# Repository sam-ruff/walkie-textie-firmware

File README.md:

# Walkie-Textie Rust Firmware

ESP32-S3 firmware with WIO-SX1262 LoRa module using Embassy async runtime. Receives COBS-encoded binary commands over serial or BLE and supports LoRa TX/RX operations.

The wire protocol (command/response codec and COBS framing) lives in the shared [`wt-protocol`](https://github.com/sam-ruff/walkie-textie-protocol) crate, vendored here as a git submodule and used by both this firmware and the phone app so the two cannot drift. Clone with submodules:

```bash
git clone --recursive <repo-url>
# or, in an existing checkout:
git submodule update --init --recursive
```

## Building

### Prerequisites

Install the ESP Rust toolchain:

```bash
cargo install espup
espup install
source ~/export-esp.sh
```

You must run `source ~/export-esp.sh` in each new terminal session before building.

### Host Tests

Run unit tests on your development machine:

```bash
cargo t
# or: cargo test --target x86_64-unknown-linux-gnu
```

### Embedded Build (ESP32-S3)

Debug build:

```bash
cargo +esp build --features embedded -Zbuild-std=core,alloc
```

Release build:

```bash
cargo +esp build --features embedded --release -Zbuild-std=core,alloc
```

### Factory test build

Radio compliance measurements need the transmitter held on, or a steady run
of identical packets, which normal traffic never gives. Adding the
`factory-test` feature builds firmware that can do both. Never ship that
build.

```bash
cargo +esp build --features embedded,factory-test --release -Zbuild-std=core,alloc
```

Type one character into the debug serial port: `c` holds an unmodulated
carrier, `m` holds continuous LoRa modulation, `p` sends 64-byte test
packets with a second of silence after each, `s` stops. All three use the
configured frequency and power. The build also advertises over Bluetooth
every 20 ms. Its host tests run with
`cargo test --target x86_64-unknown-linux-gnu --features host-test,factory-test`.
It has not been run on a board yet.

### Flash

```bash
espflash flash --port /dev/ttyACM0 target/xtensa-esp32s3-none-elf/release/walkie-textie-rust-firmware
```

Or use cargo run (configured in `.cargo/config.toml`):

```bash
cargo +esp run --features embedded --release -Zbuild-std=core,alloc
```

To flash multiple devices at once:

```bash
./flash_devices.sh                           # Auto-detect and flash all
./flash_devices.sh /dev/ttyACM0 /dev/ttyACM2 # Flash specific ports
```

**If flashing fails**, put the device in bootloader mode:
1. Hold the **BOOT** button
2. Press and release **RESET**
3. Release **BOOT** button
4. Run the flash command again

**After flashing**, unplug and replug the USB cable. Verify the device is running by checking that two serial ports appear:

```bash
ls /dev | grep ACM
# Should show: ttyACM0 ttyACM1 (for one device)
# Or: ttyACM0 ttyACM1 ttyACM2 ttyACM3 (for two devices)
```

### Monitor

The firmware exposes two USB CDC-ACM serial ports:
- **CDC0** (e.g. `/dev/ttyACM0`): Data port for commands/responses
- **CDC1** (e.g. `/dev/ttyACM1`): Debug log output

To monitor the debug output after flashing:

```bash
# Open debug port (second ttyACM device)
picocom /dev/ttyACM1 -b 115200
```

Debug output includes startup messages and LoRa/BLE events:
```
Walkie-Textie v0.1.0 starting...
Device ID: A1B2C3
Starting tasks...
LoRa: Initialising radio...
LoRa: Radio initialised
BLE: Starting as 'WalkieTextie-A1B2C3'
BLE: Advertising...
All tasks started
LoRa TX: 'Hello World'
LoRa TX: Complete
LoRa RX: 'Reply' (RSSI: -45, SNR: 8)
BLE: Connected
BLE: Disconnected
```

To monitor both ports simultaneously, use two terminals or a tool like `tmux`:
```bash
# Terminal 1: Data port (for sending commands)
picocom /dev/ttyACM0 -b 115200
# Terminal 2: Debug port (for viewing logs)
picocom /dev/ttyACM1 -b 115200
# For a second device
picocom /dev/ttyACM3 -b 115200
```

## Bootloader

This firmware uses the ESP-IDF 2nd stage bootloader. The bootloader is pre-flashed on most ESP32-S3 development boards.

### espflash.toml and fresh clones

`espflash.toml` points espflash at the silent bootloader binary under
`bootloader/build/`, which is gitignored. On a fresh clone that file does
not exist and every `espflash flash` run from the repo directory fails with
a misleading "Error while connecting to device" - espflash reads the config
from the working directory and gives no missing-file error. Either build
the bootloader first (next section), comment the override out of
`espflash.toml`, or flash from outside the repo directory to fall back to
espflash's bundled bootloader.

### Flashing the Bootloader from Scratch

If you need to flash the bootloader (e.g., on a new chip or after corruption):

1. Install espflash:
   ```bash
   cargo install espflash
   ```

2. Download the ESP-IDF bootloader binary for ESP32-S3 from the espflash releases or build from ESP-IDF.

3. Flash the bootloader and partition table:
   ```bash
   espflash write-bin 0x0 bootloader.bin --port /dev/ttyACM0
   espflash write-bin 0x8000 partition-table.bin --port /dev/ttyACM0
   ```

Alternatively, espflash can flash a complete image including bootloader:
```bash
espflash flash --port /dev/ttyACM0 --bootloader bootloader.bin --partition-table partition-table.bin target/xtensa-esp32s3-none-elf/release/walkie-textie-rust-firmware
```

### Building a Silent Bootloader

By default, the ESP-IDF bootloader outputs log messages on boot. To disable this, build a custom bootloader with logging disabled using the project in `bootloader/`:

1. Install ESP-IDF (v5.2 or later):
   ```bash
   mkdir -p ~/esp
   cd ~/esp
   git clone -b v5.2.2 --recursive https://github.com/espressif/esp-idf.git
   cd esp-idf
   ./install.sh esp32s3
   ```

2. Build the silent bootloader:
   ```bash
   source ~/esp/esp-idf/export.sh
   cd bootloader
   idf.py set-target esp32s3
   idf.py build
   cp build/bootloader/bootloader.bin ../silent-bootloader-esp32s3.bin
   ```

3. Flash with the silent bootloader:
   ```bash
   espflash flash --port /dev/ttyACM0 \
       --bootloader silent-bootloader-esp32s3.bin \
       target/xtensa-esp32s3-none-elf/release/walkie-textie-rust-firmware
   ```

### Notes on ESP-IDF Bootloader Compatibility

The firmware includes an app descriptor (`esp_app_desc!` macro) required by the ESP-IDF bootloader for validation. The efuse block revision fields are set to accept all chip revisions (min=0, max=65535).

## Integration Tests

After flashing the firmware, run integration tests to verify functionality. Cargo aliases are provided for convenience and auto-detect data ports by default:

| Alias               | Description                |
|---------------------|----------------------------|
| `cargo integration` | Single-device serial tests |
| `cargo lora`        | Two-device LoRa tests      |
| `cargo ble-serial`  | BLE tests via serial       |
| `cargo ble-ble`     | BLE-to-BLE tests           |

Port auto-detection scans ttyACM devices and identifies the data port (CDC0) by sending a GetVersion command.

### Single-Device Tests

Tests basic command/response functionality:

```bash
# Auto-detect port (default)
cargo integration

# Or specify port manually
cargo integration --port /dev/ttyACM0
```

Options:
- `--port <PORT>`: Serial port (default: auto)
- `--baud <RATE>`: Baud rate (default: 115200)

The tests verify:
- GetVersion returns firmware version
- Invalid command returns error
- Multiple sequential commands work correctly

### Two-Device LoRa Tests

Tests bidirectional LoRa communication between two flashed devices:

```bash
# Auto-detect both ports (default)
cargo lora

# Or specify ports manually
cargo lora --port-a /dev/ttyACM0 --port-b /dev/ttyACM2
```

Options:
- `--port-a <PORT>`: Serial port for device A (default: auto)
- `--port-b <PORT>`: Serial port for device B (default: auto)
- `--baud <RATE>`: Baud rate (default: 115200)

The tests verify:
- A to B transmission
- B to A transmission
- Bidirectional ping-pong
- Multiple sequential messages
- Reliability (10 round trips)

## Hardware Configuration

| Pin    | Function         |
|--------|------------------|
| GPIO7  | SPI SCLK         |
| GPIO8  | SPI MISO         |
| GPIO9  | SPI MOSI         |
| GPIO41 | LoRa NSS (CS)    |
| GPIO39 | LoRa DIO1 (IRQ)  |
| GPIO42 | LoRa NRST        |
| GPIO40 | LoRa BUSY        |
| GPIO38 | LoRa RF_SW       |
| GPIO48 | LED (active low) |

TCXO voltage: 1.8V (configured via DIO3)

RF_SW is the receive enable of the Wio-SX1262's antenna switch. The driver
holds it high while the radio listens and low while it transmits or idles,
and DIO2 selects the transmit path.

## Command Protocol

Binary protocol with COBS encoding and zero byte delimiter:

```
[COBS-encoded payload][0x00]

Payload: [version: u8][cmd_id: u8][length: u16 LE][data][crc16: u16 LE]
```

Protocol version is currently `1`. The firmware will reject commands with mismatched versions.

### Commands

| ID   | Command            | Payload              | Response    | Description                        |
|------|--------------------|----------------------|-------------|------------------------------------|
| 0x01 | GetVersion         | None                 | Version     | Returns firmware version           |
| 0x03 | Reboot             | None                 | None        | Reboots the device (no response)   |
| 0x10 | LoraTx             | Data bytes (max 256) | TxComplete  | Transmits data over LoRa           |
| 0x11 | SetSpreadingFactor | sf (u8, 7-12)        | RadioConfig | Sets the LoRa spreading factor     |
| 0x12 | GetRadioConfig     | None                 | RadioConfig | Reads the active radio config      |

### Responses

| ID   | Response    | Payload                                                             | Description                              |
|------|-------------|---------------------------------------------------------------------|------------------------------------------|
| 0x01 | Version     | major, minor, patch (3 bytes)                                       | Firmware version response                |
| 0x10 | TxComplete  | None                                                                | LoRa transmission completed successfully |
| 0x11 | RxPacket    | data, rssi (i16 LE), snr (i8)                                       | Received LoRa packet (unsolicited)       |
| 0x12 | RadioConfig | freq_hz (u32 LE), sf (u8), bw_khz (u32 LE), cr (u8), tx_power (i8)  | Active radio configuration (11 bytes)    |
| 0x13 | TxRefused   | retry_after_secs (u32 LE)                                           | TX refused by the duty cycle limiter     |
| 0xFF | Error       | status code, original command ID                                    | Error response with status and cmd ID    |

### Response Format

Responses use the same frame structure as commands:

```
Payload: [version: u8][resp_id: u8][length: u16 LE][data][crc16: u16 LE]
```

### Unsolicited Responses

The firmware continuously listens for incoming LoRa packets in the background (100ms polling interval). When a packet is received, it is immediately pushed to the host as an unsolicited `RxPacket` response.

- Response ID: `0x11`
- Sequence ID: `0` (distinguishes unsolicited from request/response pairs)
- Payload: `[data bytes][rssi: i16 LE][snr: i8]`
- Max TX latency: 100ms (radio must exit RX mode to transmit)

The host must be ready to receive these at any time.

### Response Status Codes

| Code | Status           | Description                                        |
|------|------------------|----------------------------------------------------|
| 0x00 | Success          | Command executed successfully                      |
| 0x01 | InvalidCommand   | Unknown command ID                                 |
| 0x02 | InvalidLength    | Payload length invalid for command                 |
| 0x03 | CrcError         | CRC-16 checksum mismatch                           |
| 0x04 | InvalidVersion   | Protocol version mismatch                          |
| 0x05 | InvalidParameter | Parameter out of range (e.g. SF outside 7-12)      |
| 0x10 | LoraError        | LoRa radio error during operation                  |
| 0x11 | Timeout          | Operation timed out                                |

### Radio Configuration and Duty Cycle

The radio boots at 869.525 MHz, spreading factor 10, 125 kHz bandwidth, coding
rate 4/8 and +22 dBm. The spreading factor can be changed at runtime with
`SetSpreadingFactor` (7-12); it is not persisted and reverts to SF10 on reboot.
Both radios in a link must use the same spreading factor and bandwidth, so a
radio built before the bandwidth changed from 250 kHz cannot hear one built
after.

The bandwidth is half the 250 kHz sub-band on purpose. EN 300 220-2 wants the
occupied bandwidth inside the sub-band at every spreading factor and
temperature, and a 250 kHz signal leaves no room. SF10 at 125 kHz has the same
symbol time and sensitivity as SF11 at 250 kHz, and about nine tenths of its
bit rate.

Transmissions are checked against the EU duty cycle rules (ERC 70-03) for the
sub-band containing the configured frequency; 869.4-869.65 MHz allows 10%
airtime per sliding hour (360 s). Spent airtime is tracked with the Semtech
time-on-air formula, and a `LoraTx` that would exceed the remaining budget is
refused without transmitting: the firmware replies `TxRefused` with the number
of seconds until enough budget frees up (`0xFFFFFFFF` if the packet exceeds the
entire hourly budget). At SF10 a full 255-byte packet costs about 3.57 s of
airtime, so roughly 100 of them fit in an hour; lower spreading factors are far
cheaper.

### Example Frames

All examples show the complete COBS-encoded frame including the zero delimiter.

**GetVersion Command:**
```
Raw:    01 01 00 00 84 41       (version=1, cmd=0x01, len=0, crc=0x4184)
COBS:   03 01 01 01 03 84 41 00
```

**GetVersion Response (v0.1.0):**
```
Raw:    01 01 03 00 00 01 00 22 20    (version=1, resp=0x01, len=3, payload=[0,1,0], crc=0x2022)
COBS:   04 01 01 03 01 02 01 03 22 20 00
```

**Reboot Command:**
```
Raw:    01 03 00 00 e4 2f       (version=1, cmd=0x03, len=0, crc=0x2fe4)
COBS:   03 01 03 01 03 e4 2f 00
```

**LoraTx Command ("Hello"):**
```
Raw:    01 10 05 00 48 65 6c 6c 6f e6 64    (crc=0x64e6)
COBS:   04 01 10 05 08 48 65 6c 6c 6f e6 64 00
```

**Error Response (InvalidCommand for cmd 0xFE):**
```
Raw:    01 ff 02 00 01 fe 87 cf    (status=0x01, original_cmd=0xFE, crc=0xcf87)
COBS:   04 01 ff 02 05 01 fe 87 cf 00
```

### CRC-16 Calculation

The CRC-16 uses the XMODEM polynomial (0x1021) with initial value 0x0000. The CRC is calculated over the bytes: `[version][cmd_id][length_lo][length_hi][payload...]`.

Python example:
```python
import crcmod
crc16 = crcmod.predefined.mkCrcFun('xmodem')
checksum = crc16(bytes([0x01, 0x01, 0x00, 0x00]))  # GetVersion: 0x4184
```

### COBS Encoding

COBS (Consistent Overhead Byte Stuffing) encodes data to eliminate zero bytes, using 0x00 as frame delimiter. The firmware uses the `corncobs` implementation which appends the zero delimiter automatically.

Python example:
```python
from cobs import cobs
raw_frame = bytes([0x01, 0x01, 0x00, 0x00, 0x84, 0x41])
encoded = cobs.encode(raw_frame) + b'\x00'  # Add delimiter
```

## Bluetooth LE

The firmware advertises as "WalkieTextie" and provides a Nordic UART Service (NUS) for command/response communication alongside serial.

### Nordic UART Service UUIDs

| Characteristic | UUID                                 |
|----------------|--------------------------------------|
| Service        | 6E400001-B5A3-F393-E0A9-E50E24DCCA9E |
| RX (write)     | 6E400002-B5A3-F393-E0A9-E50E24DCCA9E |
| TX (notify)    | 6E400003-B5A3-F393-E0A9-E50E24DCCA9E |

### Usage

1. Scan for and connect to "WalkieTextie"
2. Enable notifications on the TX characteristic
3. Write COBS-encoded commands to the RX characteristic
4. Receive COBS-encoded responses via TX notifications

The same binary protocol is used over BLE as over serial. Commands sent via BLE receive responses via BLE; unsolicited LoRa RX packets are only sent to serial.

Compatible apps: nRF Connect, any app supporting NUS.

## Architecture

The firmware uses esp-rtos with Embassy async tasks and channel-based communication:

- **Serial Reader Task**: Reads USB serial, parses COBS frames, sends commands to channel
- **Serial Writer Task**: Receives responses from channel, encodes and writes to USB serial
- **LoRa Task**: Continuously listens for LoRa packets (100ms polling), pushes received packets immediately to serial. Processes TX commands when available with max 100ms latency.
- **LED Task**: Flashes LED on TX/RX events via channel (non-blocking)
- **BLE Host Task**: Manages BLE advertising, connections, and Nordic UART Service. Routes commands to the same channel as serial.

Traits (`LoraRadio`, `SerialPort`) allow unit testing with mock implementations.

## CI/CD

GitHub Actions runs on every push to `main`:

1. **Test**: Runs unit tests (`cargo test`)
2. **Build**: Builds release firmware using ESP toolchain
3. **Release**: Creates GitHub releases via semantic-release

Releases are triggered by conventional commit messages:
- `feat: ...` - minor version bump
- `fix: ...` - patch version bump
- `feat!: ...` or `BREAKING CHANGE:` - major version bump

The firmware binary is attached to each GitHub release.

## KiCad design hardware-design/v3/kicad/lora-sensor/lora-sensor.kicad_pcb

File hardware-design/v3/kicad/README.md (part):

# LoRa sensor board in KiCad (V3.1)

The designer's PCB_V3 arrived as fabrication files only: Gerbers, a BOM, a
placement file and pictures. There was nothing to edit. This folder rebuilds
that board as a KiCad 10 project from those files, then applies the changes
from our review of 11 September 2026. The result is called V3.1.

The design passes every check that can be made without a board in hand, but no
board has been made from it. The designer has not seen this version and
nothing here has been sent to him. Two jobs need the real thing: tuning the
868 MHz antenna match on a VNA, and the CE tests in `CE_TESTING.md`. One
finding was about the firmware and not the board: its 250 kHz LoRa bandwidth
did not fit the 250 kHz sub-band it transmits in. The firmware now uses
125 kHz, a change that has not yet been on a board. `CE_TESTING.md` has the
figures.

JLCPCB places every part. Nothing is left to solder when the boards arrive.
One part, the LoRa module, has to be sent to JLCPCB first, because they do not
stock it.

One thing is worth knowing before a board exists. The power mux
disconnects both supplies for some microseconds each time USB is plugged in
or pulled out with a battery fitted. On a nearly flat battery, with a radio
transmitting, that can stop the converter, and the supervisor then resets the
ESP32. Firmware should expect to be restarted by a change of supply. The
figures are under "On the first boards".

## What is here

`lora-sensor/` is the KiCad project: schematic, board, and its own symbol and
footprint libraries. Open `lora-sensor.kicad_pro` with KiCad 10.

`fab/` is what goes to the factory: Gerbers and drill files (also zipped), a
BOM and a placement file with JLCPCB's column names, and PDFs of the schematic
and the assembly drawing. There are four orders, which share the Gerbers and
differ in what is fitted:

| Order | Files | What it is for |
| --- | --- | --- |
| node | `fab/BOM.csv`, `fab/CPL.csv` | The default. R37 holds the converter on, for firmware that never signals the wake timer, such as the radio firmware in this repo |
| timed | `fab/timed/` | R37 left out, so the wake timer cuts the power between readings. For firmware that signals DONE |
| antenna-test | `fab/antenna-test/` | The U.FL connector and its link fitted and the radio's link left out, for measuring the antenna on a VNA. Never power one of these |
| bench-test | `fab/bench-test/` | The U.FL connector and its link fitted and the two antenna matching parts left out, for the conducted compliance tests |

`as-delivered/` is PCB_V3 exactly as the designer delivered it, imported into
KiCad so it can be opened, measured and compared. Plotted back out, its copper
matches his Gerbers to within 4 micrometres. Running DRC on it shows his
outline, drill and thermal-relief problems directly.

`tools/` builds all of the above. `datasheets/` holds the documents the layout
and the part changes rest on: the drawings of the USB plug and of the plug the
designer used, the Pulse antenna datasheet, the TPS631000, TPS2116, TPS2595
and TLV803 datasheets, and the datasheet of the MOSFET that replaced the
brief's. `CE_TESTING.md` is how to run the compliance tests on this board.

## The project is generated

Everything in `lora-sensor/` and `fab/` is written by `tools/build.py` from
`tools/design.py`, which lists every part, its position, its nets and every
track. The board is routed by hand: each track and via is written out there
with the reason for its path, and no autorouter runs. Change the design there
and rebuild. An edit made in KiCad is lost at the next build. Two builds of
the same design write the same files, so a diff in git is a real change.

If you would rather carry on in KiCad by hand, that works too: the project is
complete and passes its checks. Stop running the build after that.

```bash
cd hardware-design/v3/kicad
uv venv --python /usr/bin/python3 --system-site-packages .venv
uv pip install --python .venv/bin/python -r tools/requirements.txt
.venv/bin/python tools/build.py
```

The Python has to be the one KiCad's `pcbnew` module is installed for, which
is why the virtual environment is allowed to see system packages. The build
takes under a minute and stops at the first failing step. A warning fails it
the same as an error. A part that is new to the BOM needs `--fetch` once, to
download JLCPCB's library entry for it. These are the checks it ends on:

- KiCad's ERC on the schematic, and DRC on the board with the board compared
  against the schematic.
- The rules the routing was drawn to. Only the feed, its match and ground go
  near the 868 MHz feed. No top-layer track runs under the ESP32 module or
  between the timer's pins. A line may have 2.5 mm of top-layer track under
  the LoRa module to reach its pad and no more. The log lists each long line
  with its length on each layer and its vias.
- The firmware in this repo against the board. The pin numbers are read from
  `src/main.rs` and each is followed to the part it has to reach, GPIO38 to
  the LoRa module's RF_SW pin among them. The level each output starts at
  is checked too.
- Every part of every order has a JLCPCB part number and a row in the
  placement file. A part with neither would be left for someone to solder.
- Every placed part against JLCPCB's own footprint for its part number, at
  the position and rotation in the placement file. A part that would be
  fitted turned shows up as pads that miss. Each connected pad's function is
  compared with JLCPCB's symbol for the part as well, so a substitute with
  another pinout is caught.
- The values that set the 3.3 V rail, the wake-up interval, the voltage at
  which the USB input's switch passes power, its current limit and how fast
  it raises its output. Each is worked out at the worst case of the
  tolerances, against the datasheet formulas. The reset supervisor's
  threshold is checked against that rail.
- The power mux: that its pins put it in the mode that passes the higher
  supply, and how far its output falls while it changes from one supply to
  the other (`tools/supply_change.py`). These two checks and the USB input
  check below run for every order that is powered, with the parts it fits,
  and hold each to the same marks.
- For an order that leaves the rail to the wake timer, what the battery
  still feeds while the rail is off, added up from the makers' figures. If
  that is over the brief's 5 uA the log prints a RISK line. It does not
  stop the build, because the capacitors' share is a limit with no typical
  figure and only a measurement settles it.
- The Gerbers and drill file themselves: one closed rectangular outline, the
  two slots for the plug's legs, a board edge at either end of its tolerance
  still letting the widest leg into them, solder paste on the plug's pads
  and on the land round each leg with none of it on bare board, the inner
  planes 0.3 mm or more from those slots, 0.1 mm or more of solder mask
  between any two openings, no hole in a pad, the antenna area clear, the
  ground plane in one piece.
- The numbers behind the radio layout: feed impedance, antenna land pattern
  and the ESP32 antenna's overhang. Then what the datasheets predict for
  radiated power and harmonics at the power the firmware sets, against the
  legal limits. It also models the firmware's LoRa signal against the
  sub-band it uses and prints a RISK line when the fit is poor. That line
  does not stop the build either, because the remedy is a firmware setting.
- What the layout decides about emissions and static discharge: the area of
  the converter's switching loops and the field they could radiate, and the
  voltage a discharge to the plug's shell puts on the capacitor behind it.
  The same step models the ring on the USB input when the board is plugged
  into a live supply, and checks that only parts rated for it are ahead of
  the protection switch. It models a plug that loses contact and makes it
  again as well, when the switch is on and the ring reaches what is behind
  it, with the mux on USB and with the mux gone back to the battery. That
  ring has to stay 5 per cent under the 6 V those parts allow, and under
  6 V with less to damp it than the model assumes.
- The battery and sensor connectors: pin 1 where JST's drawing puts it, and
  a silkscreen legend that names the net on each pad.

## Before ordering

- Send the LoRa modules to JLCPCB before placing the order. U11 has to be
  the Wio-SX1262 without the antenna connector, Seeed part 113991436. JLCPCB
  does not stock it. Their library has an entry for parts of that number
  that customers send in, C9900285183, and the BOM carries it. If JLCPCB
  gives your modules another number when they book them in, change `lcsc`
  on U11 in `tools/design.py` and rebuild. The module with the connector
  (their C55348741, none in stock on 10 November 2026) leaves the antenna
  pad unconnected and will not do. No other LoRa module JLCPCB stocks has
  this module's pads or the same control pins.
- Choose JLCPCB's standard assembly service, not the economic one. The USB
  plug (J1, C530607) is listed for standard assembly only, with a fixture,
  because its shell hangs 10.7 mm over the board edge.
- Tell JLCPCB in the order's remarks that two parts hang over the board. J1
  overhangs the left edge by 10.7 mm between 24 and 36 mm from the bottom.
  Its shell is thicker than the board: it stands about 0.15 mm below the
  bottom face, and its two legs about 0.8 mm, so no rail or tab can go
  there and the board does not lie flat. The ESP32 module's antenna
  overhangs the top edge by about 6 mm, level with the board. Let their
  engineers place the rails or the fixture to suit.
- JLCPCB's ordinary outline tolerance of 0.2 mm is enough. J1's shell stops
  against the left edge. The edge is drawn 0.1 mm back from where the
  plug's drawing has it, and each slot is 0.2 mm longer than the drawing's
  at the end nearer the edge, so that an edge cut proud still lets the legs
  in. The plug's own drawing allows its legs more variation than that
  covers. JLCPCB holds the plugs, so the first boards are where that shows.
- In the placement preview, check which way round U11 sits. Its number has
  no footprint in JLCPCB's library, so the rotation in the file was worked
  out from their entry for the module with the connector. Pad 1 is the one
  nearest the top right corner of the module's outline on the assembly
  drawing.
- Order 4 layers at 0.8 mm, which the antenna feed is sized for. The two
  slots for the plug's legs are 0.5 mm wide, the narrowest plated slot
  JLCPCB makes.
- The brief asks for lead-free HASL. ENIG is the better choice now: the
  plug's contacts are 0.27 mm pads at 0.5 mm pitch and U14 is a leadless
  package at the same pitch, and both solder more reliably on a flat
  finish. The owner has not chosen.
- When JLCPCB asks for the layer order, `In1_Cu.g1` is layer 2 (ground) and
  `In2_Cu.g2` is layer 3 (3.3 V). Solder paste is on the top face only.
- Pick the stack-up with 0.1 mm prepreg under the outer layers (JLCPCB's 3313
  family) if it is offered. The feed is 2.5 mm long, so the thicker prepreg
  would cost under 0.01 dB. It is not worth a delay.
- Pick the order. Boards that run the radio firmware from batteries need
  the default, which fits R37 (marked ALWAYS ON). That firmware never
  signals the power timer, which would otherwise drop the 3.3 V rail for
  50 ms every 15 minutes. A sensor whose firmware signals DONE needs the
  timed order, which leaves R37 out and changes nothing else.
- Run `.venv/bin/python tools/jlc_stock.py fab/BOM.csv 25` for today's stock
  at JLCPCB (25 is the number of boards). On 10 November 2026 every line
  JLCPCB supplies was in stock for 25 boards. The thinnest were the timer at
  416, the USB switch at 1174, the plug at 1242 and the antenna at 1970.
- Flash firmware that drives GPIO38, the LoRa module's RF_SW pin. The
  firmware in this repo does since 10 November 2026: high to receive, low
  to transmit and to idle, which is what Seeed's datasheet for the module
  asks. Older firmware leaves the pin alone, and R25 then holds it high
  all the time.
- The antenna match (L5, L6, with L7 unfitted) starts from the values in the
  Pulse datasheet. Tune it on a VNA on the real board, in its enclosure. The
  steps are in `hardware-design/CLAUDE.md`. A couple of boards from the
  antenna-test order arrive ready to measure: the test link R31 and the
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
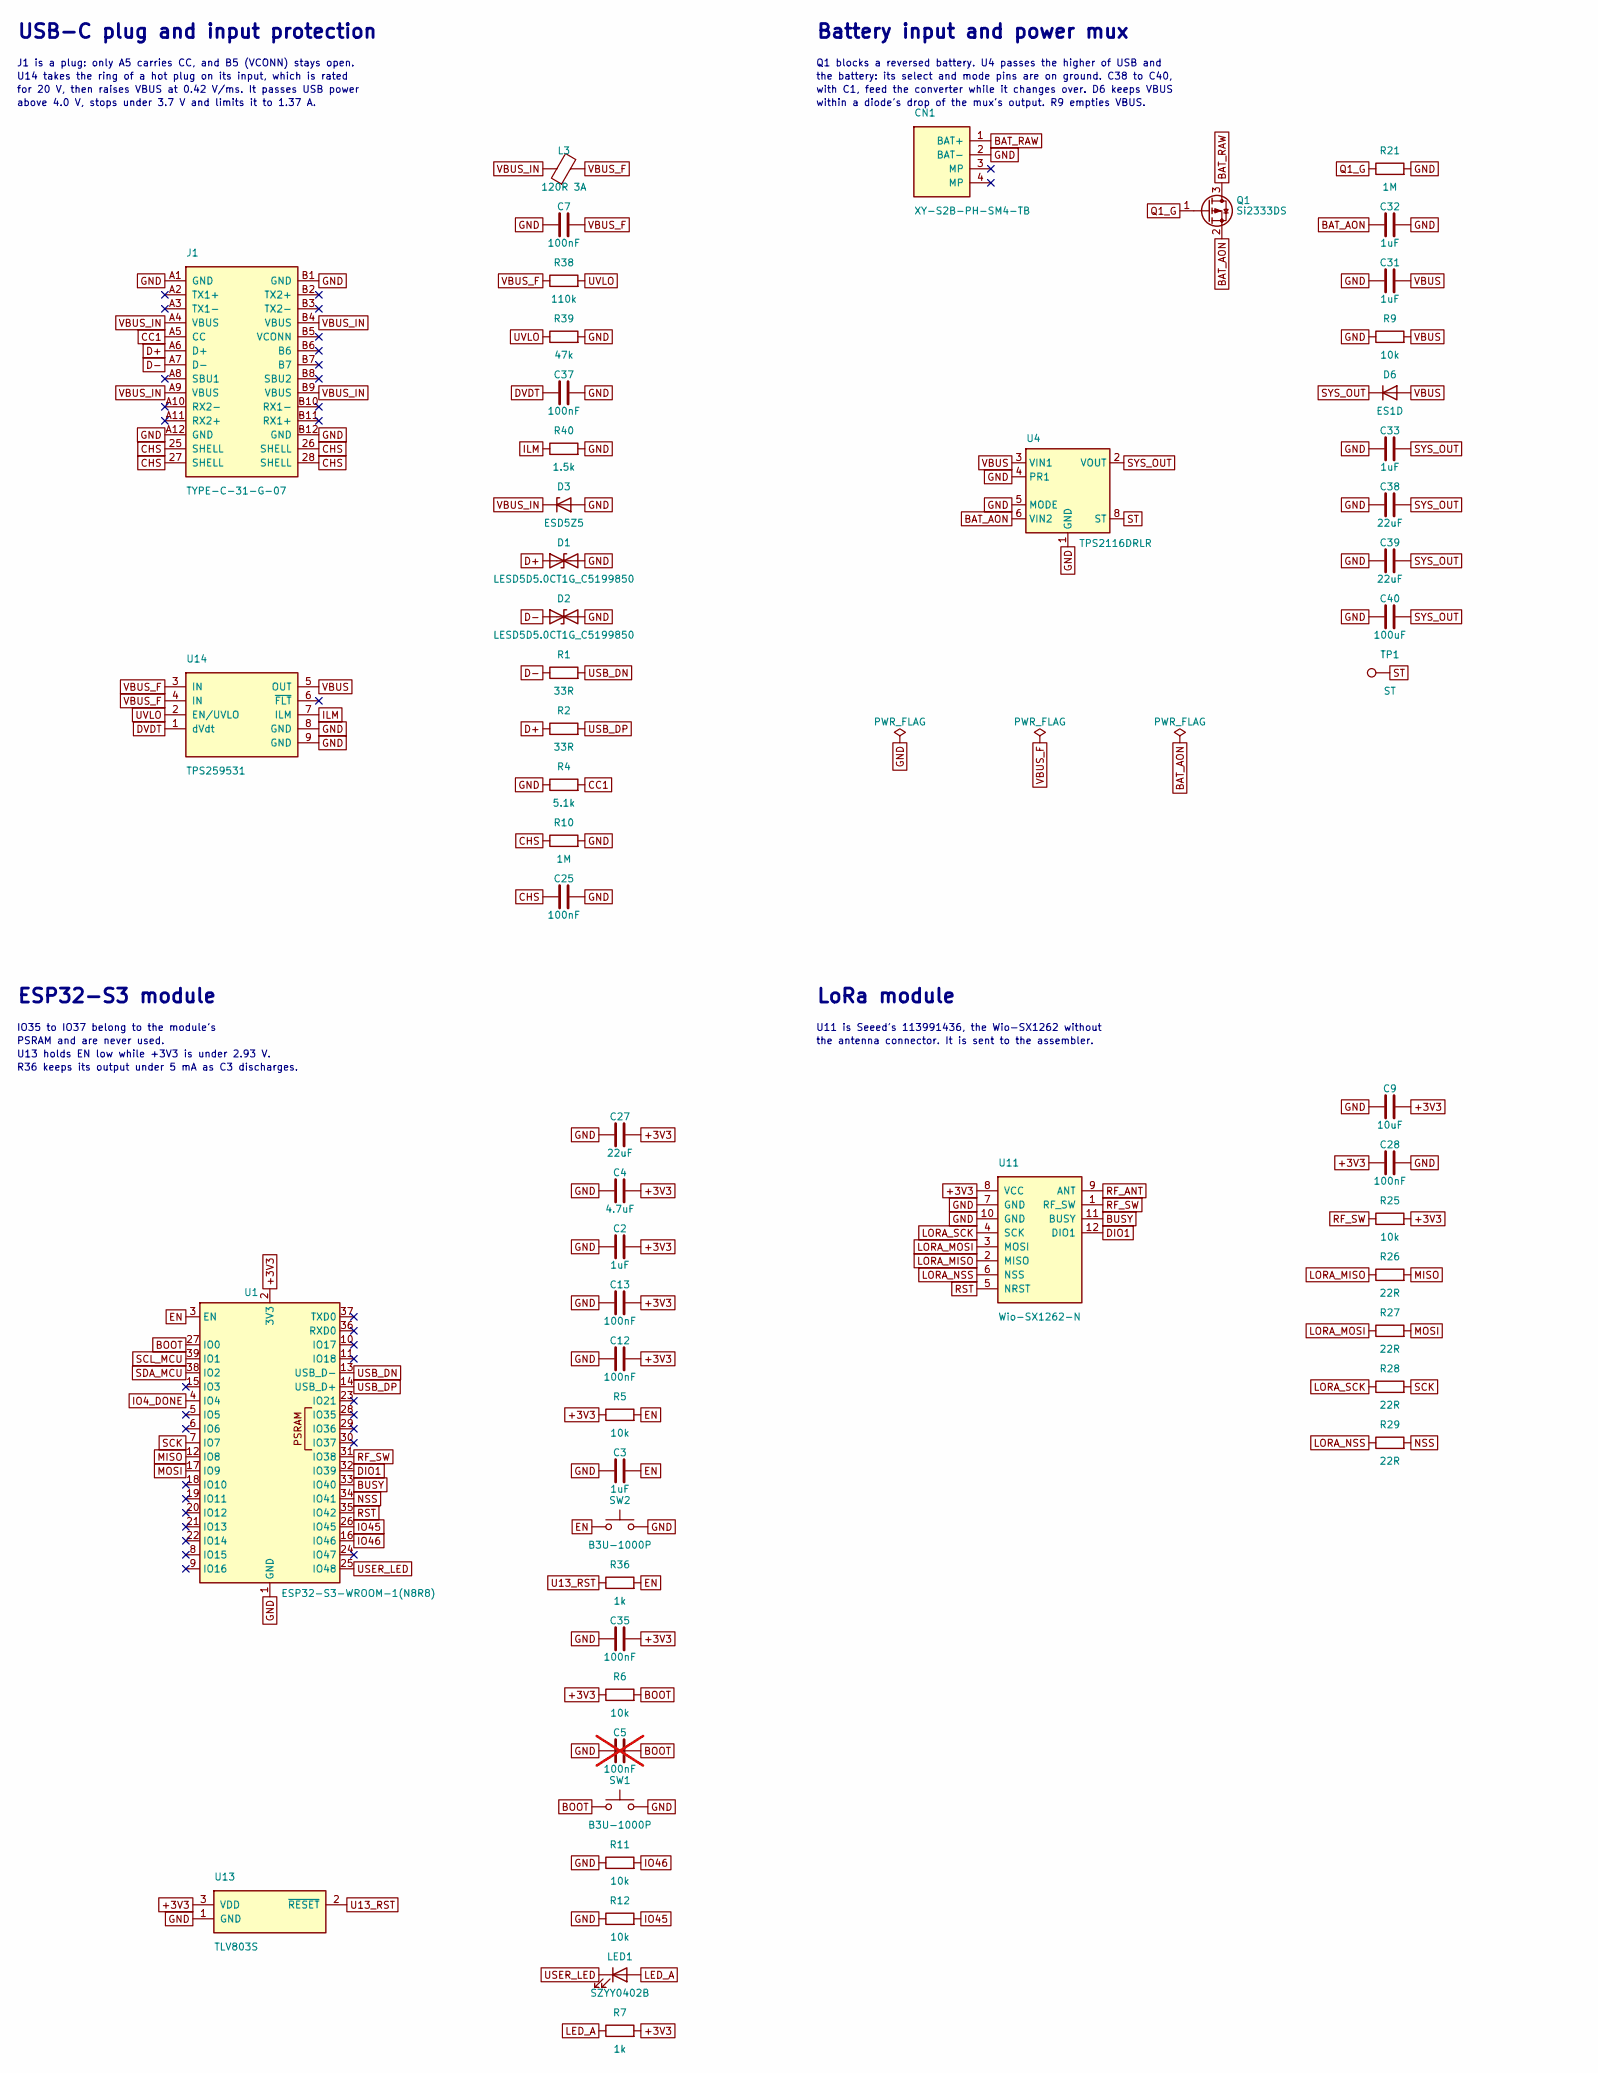
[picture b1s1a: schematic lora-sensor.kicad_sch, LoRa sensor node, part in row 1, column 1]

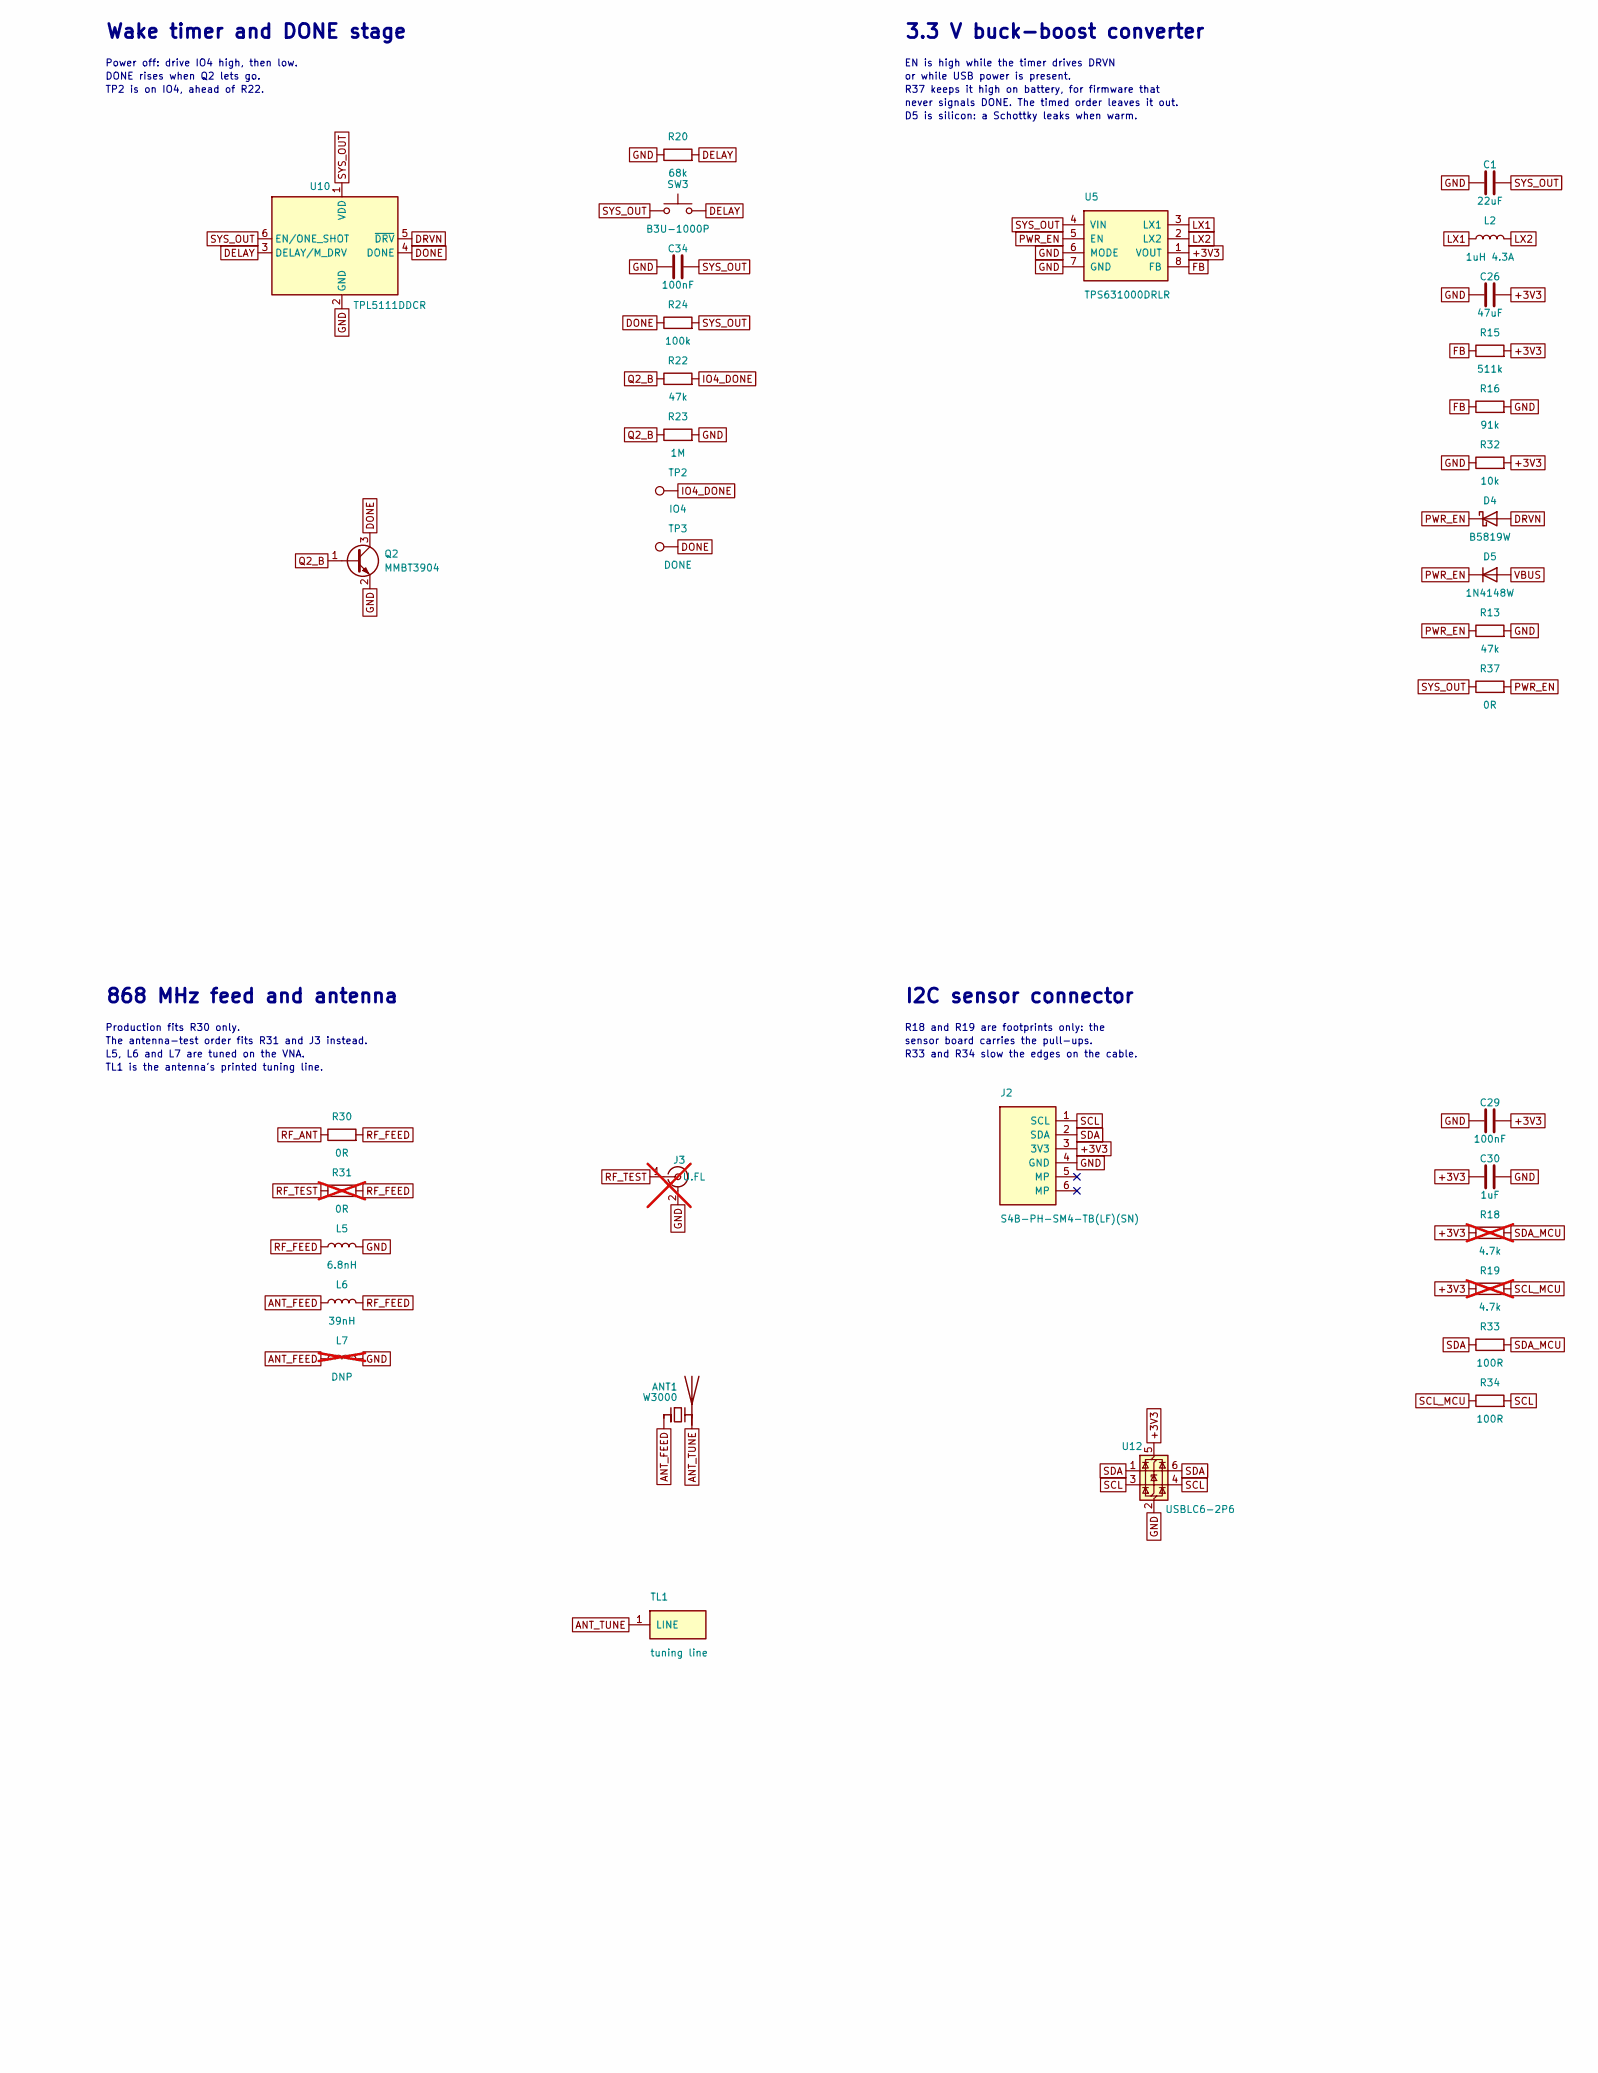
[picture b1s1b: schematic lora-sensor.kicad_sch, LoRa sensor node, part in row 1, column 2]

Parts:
ANT1: W3000; Pulse_W3000; MPN W3000; LCSC C515701
C1, C27, C38, C39: 22uF; C_0805_2012Metric; MPN CL21A226MAQNNNE; LCSC C45783
C2, C3, C30, C31, C32, C33: 1uF; C0402; MPN CL05A105KA5NQNC; LCSC C52923
C4: 4.7uF; C0402; MPN TCC0402X5R475M6R3AT; LCSC C380302
C5: 100nF; C0402; MPN CC0402KRX7R7BB104; LCSC C60474; not fitted
C7, C12, C13, C25, C28, C29, C34, C35, C37: 100nF; C0402; MPN CL05B104KB54PNC; LCSC C307331
C9: 10uF; C_0603_1608Metric; MPN CL10A106KP8NNNC; LCSC C19702
C26: 47uF; C_0805_2012Metric; MPN CL21A476MQYNNNE; LCSC C16780
C40: 100uF; C_1206_3216Metric; MPN CL31A107MQHNNNE; LCSC C15008
CN1: XY-S2B-PH-SM4-TB; CONN-SMD_P2.00_S2B-PH-SM4-TB-LF-SN; MPN XY-S2B-PH-SM4-TB; LCSC C54582899
D1, D2: LESD5D5.0CT1G_C5199850; SOD-523_L1.2-W0.8-LS1.6-BI; MPN LESD5D5.0CT1G; LCSC C5199850
D3: ESD5Z5; SOD-523_L1.2-W0.8-LS1.6-RD-2; MPN ESD5Z5.0T1G; LCSC C5199848
D4: B5819W; SOD-123_L2.7-W1.6-LS3.7-RD; MPN B5819W SL; LCSC C8598
D5: 1N4148W; SOD-123_L2.7-W1.6-LS3.7-RD; MPN 1N4148W; LCSC C81598
D6: ES1D; D_SOD-123F; MPN ES1DL; LCSC C2923901
J1: TYPE-C-31-G-07; USB-C_Plug_HRO_TYPE-C-31-G-07; MPN TYPE-C-31-G-07; LCSC C530607
J2: S4B-PH-SM4-TB(LF)(SN); CONN-SMD_S4B-PH-SM4-TB-LF-SN; MPN S4B-PH-SM4-TB(LF)(SN); LCSC C265102
J3: U.FL; U.FL_Hirose_U.FL-R-SMT-1_Vertical; MPN U.FL-R-SMT-1(10); LCSC C88373; not fitted
L2: 1uH 4.3A; L_1008_2520Metric; MPN DFE252012P-1R0M=P2; LCSC C882955
L3: 120R 3A; L_0603_1608Metric; MPN BLM18KG121TN1D; LCSC C85831
L5: 6.8nH; L0603; MPN VHF160808H6N8JT; LCSC C90203
L6: 39nH; L0603; MPN LQW18AN39NG00D; LCSC C86134
L7: DNP; L0603; not fitted
LED1: SZYY0402B; LED0402-RD_BLUE; MPN SZYY0402B; LCSC C434447
Q1: Si2333DS; SOT-23; MPN SI2333DS-T1-GE3; LCSC C727544
Q2: MMBT3904; SOT-23; MPN MMBT3904LT1G; LCSC C81464
R1, R2: 33R; R0402; MPN RC0402FR-0733RL; LCSC C138002
R4: 5.1k; R0402; MPN 0402WGF5101TCE; LCSC C25905
R5, R6, R9, R11, R12, R25, R32: 10k; R0402; MPN 0402WGF1002TCE; LCSC C25744
R7, R36: 1k; R0402; MPN 0402WGF1001TCE; LCSC C11702
R10, R21, R23: 1M; R0402; MPN 0402WGF1004TCE; LCSC C26083
R13, R22, R39: 47k; R0402; MPN 0402WGF4702TCE; LCSC C25792
R15: 511k; R0402; MPN FRC0402F5113TS; LCSC C5126239
R16: 91k; R0402; MPN FRC0402F9102TS; LCSC C2909393
R18, R19: 4.7k; R0402; MPN 0402WGF4701TCE; LCSC C25900; not fitted
R20: 68k; R0402; MPN FRC0402F6802TS; LCSC C2909379
R24: 100k; R0402; MPN 0402WGF1003TCE; LCSC C25741
R26, R27, R28, R29: 22R; R0402; MPN 0402WGF220JTCE; LCSC C25092
R30, R37: 0R; R0402; MPN 0402WGF0000TCE; LCSC C17168
R31: 0R; R0402; MPN 0402WGF0000TCE; LCSC C17168; not fitted
R33, R34: 100R; R0402; MPN 0402WGF1000TCE; LCSC C25076
R38: 110k; R0402; MPN 0402WGF1103TCE; LCSC C25745
R40: 1.5k; R0402; MPN 0402WGF1501TCE; LCSC C25867
SW1, SW2, SW3: B3U-1000P; KEY-SMD_B3U-1000PM; MPN B3U-1000P; LCSC C231329
TL1: tuning line; W3000_Tuning_Line
TP1: ST; TestPoint_Pad_D1.0mm
TP2: IO4; TestPoint_Pad_D1.0mm
TP3: DONE; TestPoint_Pad_D1.0mm
U1: ESP32-S3-WROOM-1(N8R8); WIRELM-SMD_ESP32-S3-WROOM-1; MPN ESP32-S3-WROOM-1-N8R8; LCSC C2913201
U4: TPS2116DRLR; SOT-583-8_L2.1-W1.6-P0.50-LS1.6-BL; MPN TPS2116DRLR; LCSC C3235557
U5: TPS631000DRLR; SOT-583-8_L2.1-W1.2-P0.50-LS1.6-BL; MPN TPS631000DRLR; LCSC C5219190
U10: TPL5111DDCR; TSOT-23-6_L2.9-W1.6-P0.95-LS2.8-BL; MPN TPL5111DDCR; LCSC C2870554
U11: Wio-SX1262-N; Seeed_Wio-SX1262; MPN 113991436; LCSC C9900285183
U12: USBLC6-2P6; SOT-666; MPN USBLC6-2P6; LCSC C15999
U13: TLV803S; SOT-23; MPN TLV803SDBZR; LCSC C132016
U14: TPS259531; Texas_DSG0008A_WSON-8-1EP_2x2mm_P0.5mm_EP0.9x1.6mm; MPN TPS259531DSGR; LCSC C2155674

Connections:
+3V3: C2.2, C4.2, C9.2, C12.2, C13.2, C26.2, C27.2, C28.1, C29.2, C30.1, C35.2, J2.3 (3V3), R5.1, R6.1, R7.2, R15.2, R18.1, R19.1, R25.2, R32.2, U1.2 (3V3), U5.1 (VOUT), U11.8 (VCC), U12.5 (VBUS), U13.3 (VDD)
ANT_FEED: ANT1.1 (FEED), L6.1, L7.1
ANT_TUNE: ANT1.2 (PCB_Trace), TL1.1
BAT_AON: C32.1, Q1.2 (S), U4.6 (VIN2)
BAT_RAW: CN1.1 (BAT+), Q1.3 (D)
BOOT: C5.2, R6.2, SW1.1, U1.27 (IO0)
BUSY: U1.33 (IO40), U11.11 (BUSY)
CC1: J1.A5 (CC), R4.2
CHS: C25.1, J1.25 (SHELL), J1.26 (SHELL), J1.27 (SHELL), J1.28 (SHELL), R10.1
D+: D1.1 (A1), J1.A6 (D+), R2.1
D-: D2.1 (A1), J1.A7 (D-), R1.1
DELAY: R20.2, SW3.2, U10.3 (DELAY/M_DRV)
DIO1: U1.32 (IO39), U11.12 (DIO1)
DONE: Q2.3 (C), R24.1, TP3.1, U10.4 (DONE)
DRVN: D4.2 (A), U10.5 (~DRV)
DVDT: C37.1, U14.1 (dVdt)
EN: C3.2, R5.2, R36.2, SW2.1, U1.3 (EN)
FB: R15.1, R16.1, U5.8 (FB)
GND: C1.1, C2.1, C3.1, C4.1, C5.1, C7.1, C9.1, C12.1, C13.1, C25.2, C26.1, C27.1, C28.2, C29.1, C30.2, C31.1, C32.2, C33.1, C34.1, C35.1, C37.2, C38.1, C39.1, C40.1, CN1.2 (BAT-), D1.2 (A2), D2.2 (A2), D3.2 (A), J1.A1 (GND), J1.A12 (GND), J1.B1 (GND), J1.B12 (GND), J2.4 (GND), J3.2 (Ext), L5.2, L7.2, Q2.2 (E), R4.1, R9.1, R10.2, R11.1, R12.1, R13.2, R16.2, R20.1, R21.2, R23.2, R32.1, R39.2, R40.2, SW1.2, SW2.2, U1.1 (GND), U1.40 (GND), U1.41 (GND), U4.1 (GND), U4.4 (PR1), U4.5 (MODE), U5.6 (MODE), U5.7 (GND), U10.2 (GND), U11.7 (GND), U11.10 (GND), U12.2 (GND), U13.1 (GND), U14.8 (GND), U14.9 (GND)
ILM: R40.1, U14.7 (ILM)
IO4_DONE: R22.2, TP2.1, U1.4 (IO4)
IO45: R12.2, U1.26 (IO45)
IO46: R11.2, U1.16 (IO46)
LED_A: LED1.2 (A), R7.1
LORA_MISO: R26.1, U11.2 (MISO)
LORA_MOSI: R27.1, U11.3 (MOSI)
LORA_NSS: R29.1, U11.6 (NSS)
LORA_SCK: R28.1, U11.4 (SCK)
LX1: L2.1, U5.3 (LX1)
LX2: L2.2, U5.2 (LX2)
MISO: R26.2, U1.12 (IO8)
MOSI: R27.2, U1.17 (IO9)
NSS: R29.2, U1.34 (IO41)
PWR_EN: D4.1 (K), D5.1 (K), R13.1, R37.2, U5.5 (EN)
Q1_G: Q1.1 (G), R21.1
Q2_B: Q2.1 (B), R22.1, R23.1
RF_ANT: R30.1, U11.9 (ANT)
RF_FEED: L5.1, L6.2, R30.2, R31.2
RF_SW: R25.1, U1.31 (IO38), U11.1 (RF_SW)
RF_TEST: J3.1 (In), R31.1
RST: U1.35 (IO42), U11.5 (NRST)
SCK: R28.2, U1.7 (IO7)
SCL: J2.1 (SCL), R34.2, U12.3 (I/O2), U12.4 (I/O2)
SCL_MCU: R19.2, R34.1, U1.39 (IO1)
SDA: J2.2 (SDA), R33.1, U12.1 (I/O1), U12.6 (I/O1)
SDA_MCU: R18.2, R33.2, U1.38 (IO2)
ST: TP1.1, U4.8 (ST)
SYS_OUT: C1.2, C33.2, C34.2, C38.2, C39.2, C40.2, D6.1 (K), R24.2, R37.1, SW3.1, U4.2 (VOUT), U4.7 (VOUT), U5.4 (VIN), U10.1 (VDD), U10.6 (EN/ONE_SHOT)
U13_RST: R36.1, U13.2 (~RESET)
USB_DN: R1.2, U1.13 (USB_D-)
USB_DP: R2.2, U1.14 (USB_D+)
USER_LED: LED1.1 (K), U1.25 (IO48)
UVLO: R38.2, R39.1, U14.2 (EN/UVLO)
VBUS: C31.2, D5.2 (A), D6.2 (A), R9.2, U4.3 (VIN1), U14.5 (OUT)
VBUS_F: C7.2, L3.2, R38.1, U14.3 (IN), U14.4 (IN)
VBUS_IN: D3.1 (K), J1.A4 (VBUS), J1.A9 (VBUS), J1.B4 (VBUS), J1.B9 (VBUS), L3.1

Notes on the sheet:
USB-C plug and input protection
J1 is a plug: only A5 carries CC, and B5 (VCONN) stays open.
U14 takes the ring of a hot plug on its input, which is rated
for 20 V, then raises VBUS at 0.42 V/ms. It passes USB power
above 4.0 V, stops under 3.7 V and limits it to 1.37 A.
Battery input and power mux
Q1 blocks a reversed battery. U4 passes the higher of USB and
the battery: its select and mode pins are on ground. C38 to C40,
with C1, feed the converter while it changes over. D6 keeps VBUS
within a diode's drop of the mux's output. R9 empties VBUS.
Wake timer and DONE stage
Power off: drive IO4 high, then low.
DONE rises when Q2 lets go.
TP2 is on IO4, ahead of R22.
3.3 V buck-boost converter
EN is high while the timer drives DRVN
or while USB power is present.
R37 keeps it high on battery, for firmware that
never signals DONE. The timed order leaves it out.
D5 is silicon: a Schottky leaks when warm.
ESP32-S3 module
IO35 to IO37 belong to the module's
PSRAM and are never used.
U13 holds EN low while +3V3 is under 2.93 V.
R36 keeps its output under 5 mA as C3 discharges.
LoRa module
U11 is Seeed's 113991436, the Wio-SX1262 without
the antenna connector. It is sent to the assembler.
868 MHz feed and antenna
Production fits R30 only.
The antenna-test order fits R31 and J3 instead.
L5, L6 and L7 are tuned on the VNA.
TL1 is the antenna's printed tuning line.
I2C sensor connector
R18 and R19 are footprints only: the
sensor board carries the pull-ups.
R33 and R34 slow the edges on the cable.

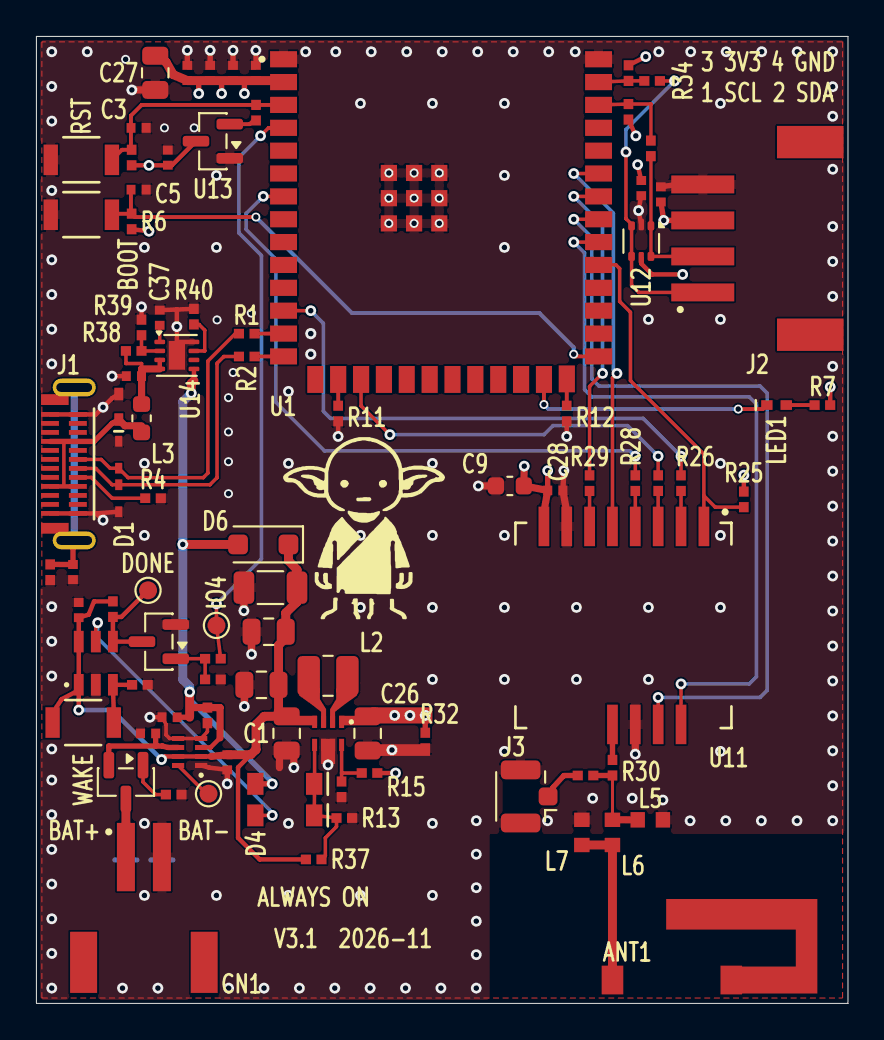
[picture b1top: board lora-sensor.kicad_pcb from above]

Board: 4 copper layers, 45.1 x 53.7 mm, 94 parts (0 on the bottom side), 56 nets.

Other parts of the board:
G1: Logo_Goblin

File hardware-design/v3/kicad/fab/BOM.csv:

"Comment","Designator","Footprint","LCSC Part #","MPN","Manufacturer","Qty"
"W3000","ANT1","lora-sensor:Pulse_W3000","C515701","W3000","Pulse","1"
"22uF","C1,C27,C38,C39","Capacitor_SMD:C_0805_2012Metric","C45783","CL21A226MAQNNNE","SAMSUNG","4"
"1uF","C2,C3,C30,C31,C32,C33","PCB_V3:C0402","C52923","CL05A105KA5NQNC","SAMSUNG","6"
"4.7uF","C4","PCB_V3:C0402","C380302","TCC0402X5R475M6R3AT","CCTC","1"
"100nF","C7,C12,C13,C25,C28,C29,C34,C35,C37","PCB_V3:C0402","C307331","CL05B104KB54PNC","SAMSUNG","9"
"10uF","C9","Capacitor_SMD:C_0603_1608Metric","C19702","CL10A106KP8NNNC","SAMSUNG","1"
"47uF","C26","Capacitor_SMD:C_0805_2012Metric","C16780","CL21A476MQYNNNE","SAMSUNG","1"
"100uF","C40","Capacitor_SMD:C_1206_3216Metric","C15008","CL31A107MQHNNNE","SAMSUNG","1"
"XY-S2B-PH-SM4-TB","CN1","PCB_V3:CONN-SMD_P2.00_S2B-PH-SM4-TB-LF-SN","C54582899","XY-S2B-PH-SM4-TB","XYECONN","1"
"LESD5D5.0CT1G_C5199850","D1,D2","PCB_V3:SOD-523_L1.2-W0.8-LS1.6-BI","C5199850","LESD5D5.0CT1G","UMW","2"
"ESD5Z5","D3","PCB_V3:SOD-523_L1.2-W0.8-LS1.6-RD-2","C5199848","ESD5Z5.0T1G","UMW","1"
"B5819W","D4","PCB_V3:SOD-123_L2.7-W1.6-LS3.7-RD","C8598","B5819W SL","CJ","1"
"1N4148W","D5","PCB_V3:SOD-123_L2.7-W1.6-LS3.7-RD","C81598","1N4148W","Semtech Electronics","1"
"ES1D","D6","lora-sensor:D_SOD-123F","C2923901","ES1DL","CJ","1"
"TYPE-C-31-G-07","J1","lora-sensor:USB-C_Plug_HRO_TYPE-C-31-G-07","C530607","TYPE-C-31-G-07","Korean Hroparts Elec","1"
"S4B-PH-SM4-TB(LF)(SN)","J2","PCB_V3:CONN-SMD_S4B-PH-SM4-TB-LF-SN","C265102","S4B-PH-SM4-TB(LF)(SN)","JST","1"
"1uH 4.3A","L2","Inductor_SMD:L_1008_2520Metric","C882955","DFE252012P-1R0M=P2","Murata","1"
"120R 3A","L3","Inductor_SMD:L_0603_1608Metric","C85831","BLM18KG121TN1D","Murata","1"
"6.8nH","L5","PCB_V3:L0603","C90203","VHF160808H6N8JT","FH","1"
"39nH","L6","PCB_V3:L0603","C86134","LQW18AN39NG00D","Murata","1"
"SZYY0402B","LED1","PCB_V3:LED0402-RD_BLUE","C434447","SZYY0402B","yongyu","1"
"Si2333DS","Q1","Package_TO_SOT_SMD:SOT-23","C727544","SI2333DS-T1-GE3","VISHAY","1"
"MMBT3904","Q2","Package_TO_SOT_SMD:SOT-23","C81464","MMBT3904LT1G","onsemi","1"
"33R","R1,R2","PCB_V3:R0402","C138002","RC0402FR-0733RL","YAGEO","2"
"5.1k","R4","PCB_V3:R0402","C25905","0402WGF5101TCE","UNI-ROYAL","1"
"10k","R5,R6,R9,R11,R12,R25,R32","PCB_V3:R0402","C25744","0402WGF1002TCE","UNI-ROYAL","7"
"1k","R7,R36","PCB_V3:R0402","C11702","0402WGF1001TCE","UNI-ROYAL","2"
"1M","R10,R21,R23","PCB_V3:R0402","C26083","0402WGF1004TCE","UNI-ROYAL","3"
"47k","R13,R22,R39","PCB_V3:R0402","C25792","0402WGF4702TCE","UNI-ROYAL","3"
"511k","R15","PCB_V3:R0402","C5126239","FRC0402F5113TS","FOJAN","1"
"91k","R16","PCB_V3:R0402","C2909393","FRC0402F9102TS","FOJAN","1"
"68k","R20","PCB_V3:R0402","C2909379","FRC0402F6802TS","FOJAN","1"
"100k","R24","PCB_V3:R0402","C25741","0402WGF1003TCE","UNI-ROYAL","1"
"22R","R26,R27,R28,R29","PCB_V3:R0402","C25092","0402WGF220JTCE","UNI-ROYAL","4"
"0R","R30,R37","PCB_V3:R0402","C17168","0402WGF0000TCE","UNI-ROYAL","2"
"100R","R33,R34","PCB_V3:R0402","C25076","0402WGF1000TCE","UNI-ROYAL","2"
"110k","R38","PCB_V3:R0402","C25745","0402WGF1103TCE","UNI-ROYAL","1"
"1.5k","R40","PCB_V3:R0402","C25867","0402WGF1501TCE","UNI-ROYAL","1"
"B3U-1000P","SW1,SW2,SW3","PCB_V3:KEY-SMD_B3U-1000PM","C231329","B3U-1000P","OMRON","3"
"ESP32-S3-WROOM-1(N8R8)","U1","PCB_V3:WIRELM-SMD_ESP32-S3-WROOM-1","C2913201","ESP32-S3-WROOM-1-N8R8","ESPRESSIF","1"
"TPS2116DRLR","U4","PCB_V3:SOT-583-8_L2.1-W1.6-P0.50-LS1.6-BL","C3235557","TPS2116DRLR","TI","1"
"TPS631000DRLR","U5","PCB_V3:SOT-583-8_L2.1-W1.2-P0.50-LS1.6-BL","C5219190","TPS631000DRLR","TI","1"
"TPL5111DDCR","U10","PCB_V3:TSOT-23-6_L2.9-W1.6-P0.95-LS2.8-BL","C2870554","TPL5111DDCR","TI","1"
"Wio-SX1262-N","U11","lora-sensor:Seeed_Wio-SX1262","C9900285183","113991436","Seeed Studio","1"
"USBLC6-2P6","U12","Package_TO_SOT_SMD:SOT-666","C15999","USBLC6-2P6","STMicroelectronics","1"
"TLV803S","U13","Package_TO_SOT_SMD:SOT-23","C132016","TLV803SDBZR","Texas Instruments","1"
"TPS259531","U14","Package_SON:Texas_DSG0008A_WSON-8-1EP_2x2mm_P0.5mm_EP0.9x1.6mm","C2155674","TPS259531DSGR","Texas Instruments","1"
